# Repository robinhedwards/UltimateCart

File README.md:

Ultimate Cart
=============
The Ultimate Cart is an SD-card based multicart for the Atari 8-bit, which I've been developing for the last few months.
It allows you to browse the SD card on the atari and launch cartridge images from ROM and CAR files from the menu.
The PCB is designed to fit in a standard grey cartridge case (after a bit of modification with some clippers and a file).

It supports most ROMs up to 1 megabyte in size, including standard 8k and 16k cartridges, XEGS, AtariMax 1 & 8mbit ROMs,
SIC! Cart, Bounty Bob, OSS, SDX & Williams. ROM dumps can be easily converted into CAR format with my html/javascript
conversion utility, [RomToCar](http://htmlpreview.github.com/?https://github.com/robinhedwards/UltimateCart/master/RomToCar.html).

Update (Feb-2016)
-----------------
New firmware also allows XEX files (Atari executables) to be launched direct from the SD card.

PCB Images
----------

Bill of Materials
-----------------

The FPGA originally used was an engineering sample (ES) variant of the chip. The production version of the FPGA is now available
and can be used instead. The programming files for the ES seem to work fine on the production chip.

```
1 x PCB (eagle .brd file can be uploaded to e.g. OSH park)
1 x Altera 10M08SAE144C8G or ES variant (Mouser part #989-10M08SAE144C8G/ES)
1 x Alliance Memory AS6C8008-55ZIN (Mouser part #913-AS6C8008-55ZIN)
4 x IDT QS3245QG (Mouser part #972-QS3245QG)
1 x 1N4148 Diode SOD-123 (e.g. RS Stock # 700-3671)
1 x Abracon ASE-50.000MHZ-ET (Farnell order code #2467898)
1 x LD1117S33TR (Farnell order code #1202826)
1 x TE Connectivity 2041021-3 or -4 (Farnell order code #2112526, Mouser part #571-2041021-1)
1 x Shrouded box header 2x5 (e.g. Hobbytronics.co.uk - BOXHEAD25, Farnell order code #2215304)
1 x Momentary tactile switch Right Angled PCB Mount (ebay)
3 x 10uF 0805 Capacitors (e.g. Farnell order code #2320856)
11 x 0.1uF 0805 Capacitors (e.g. Farnell order code #1759143)
1 x 0.01uF 0805 Capacitor (e.g. Farnell order code #1759246)
9 x 10k 0805 Resistor (e.g. Farnell order code #2447553)
1 x 0805 LED (e.g. Farnell order code #1581239)
1 x 200ohm 0805 Resistor (e.g. Farnell order code #2447602)
1 x Header male 2x1 0.1" pitch
1 x 47k 0805 Resistor (e.g. Farnell order code #2447664) [v3 Board only]
```

Assembly
--------

Although the schematic, board file and assembled images above are probably sufficient by themselves
for a determined person to complete the board, here is the method I'm using to assemble the boards.

You will need:
```
Solder paste (I used standard chipquik unleaded) syringe
Some way of reflowing the board (e.g. cheap toaster oven)
Solder paste stencil for the fpga side (optional, but recommended - see below)
Tweezers (or a better tool) for placing the components
Soldering iron
Flux and braid to fix any bridged pins (you may not need if you use a stencil)
USB Blaster to program the fpga
Blu-tac I find useful for keeping things steady
```

You can either apply solder paste by hand (using a syringe) or using a stencil. Having done it both ways,
I'd say the ten pounds I spent on a stencil was the best money I've ever spent! You can get a stencil made
cheaply from a variety of places. I'd recommend either oshstencils (USA) or smtstencil.co.uk (UK). The
paste layer was not correct on the original board, but was corrected in the revised version.

Apply the solder paste to the fpga side of the board, making sure you don't forget the ground pad. The
revised board removes R11 (a pullup resistor on the SD card line) which is not required (since SD cards
have an internal pull-up on CS).

Then populate the components, with reference to the marks on the board and the images above.
Bake the board in an over until the paste melts (you'll see it shine), leave it for about 30s-1min, then open
the oven door and let it cool.

Apply solder paste to the other side of the board (leaving the SD card which is hand soldered). There is
less need for a stencil for this side of the board, a syringe is fine. Populate (make sure you get the polarity
of the LED and diode correct) and bake again.

Before you do any hand soldering, check for bridged pins on the ICs. Some pins are bridged on the PCB - thats ok.
Any others, use braid, flux and soldering iron to remove.

Next you will need to hand solder the jtag box header (slot facing outwards), and 2x1 male header.

Now is a good time to check for shorts - (1) between the +5V and GND pins of the male header, (2) between +3.3v
and GND on the regulator, and (3) between VCC and GND on the IDT quickswitches. If you find a short then STOP
and fix it. There will be a bridge somewhere. Refer to the eagle files to help identify the location.

Once that's done, you should be able to power up the board, plug in a USB blaster and program the chip from
Quartus (use the pof file - this permanently programs the chip). If successful you should see the LED on the
board blinking.

Finally, hand solder the SD card slot and reset button to the board. You're done!

Erratum (20-Oct-15)
-------
Someone who has built this project got in touch to report that some SD cards fail to be recognised.
It appears that a 10k-100k pullup is required on the SD card DO (pin 7), or some cards will fail to initialise.
I haven't come across this in the 10 different SD cards I've tested, but if you do have problems then you can fix
it by adding a 47k pull-up resistor as shown in the photo below.

Note (1-Mar-16) - I have now uploaded a revised version of the board (v3) which adds this resistor to the PCB (labelled R11).

3d Printed Cartridge Shell (13-Jul-17)
-------
I have added STL files (and the source files) so you can use a 3d printer to make a nice cartridge shell for your PCB.

Credits
-------
* Design, PCB & FPGA firmware by Robin Edwards (electrotrains at atariage)
* Atari boot menu & XEX loader by Jonathan Halliday (flashjazzcat at atariage)
* Debugging - Matthias Reichl (HiassofT at atariage)
* Help, suggestions and FAT32 LFN code from Mark Watson (foft at atariage)

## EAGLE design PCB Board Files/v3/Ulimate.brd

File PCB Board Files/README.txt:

Eagle files for the PCB.

v2 removes an un-needed pull-up resistor on the SD card CS line.
It also includes fixes to the paste layer so you can order a stencil from the board file.
Finally, it adds a funky logo to the top of the board to match the label.

v3 adds a 47k pull-up resistor (marked R11) to SD card as discussed in the erratum on the main page. R11 is on the SD card side of the board, near the SD card slot itself.

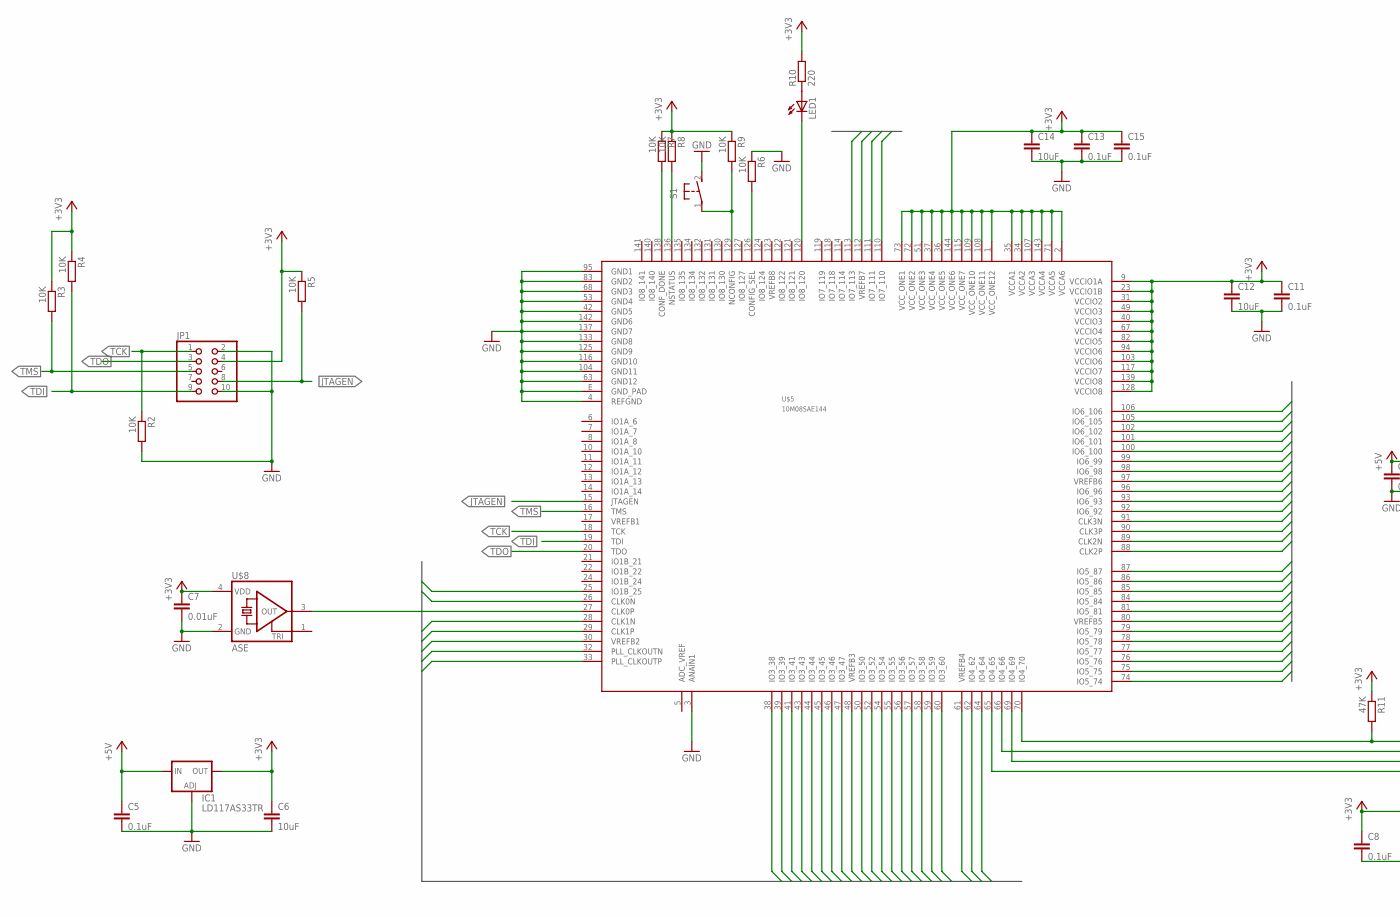
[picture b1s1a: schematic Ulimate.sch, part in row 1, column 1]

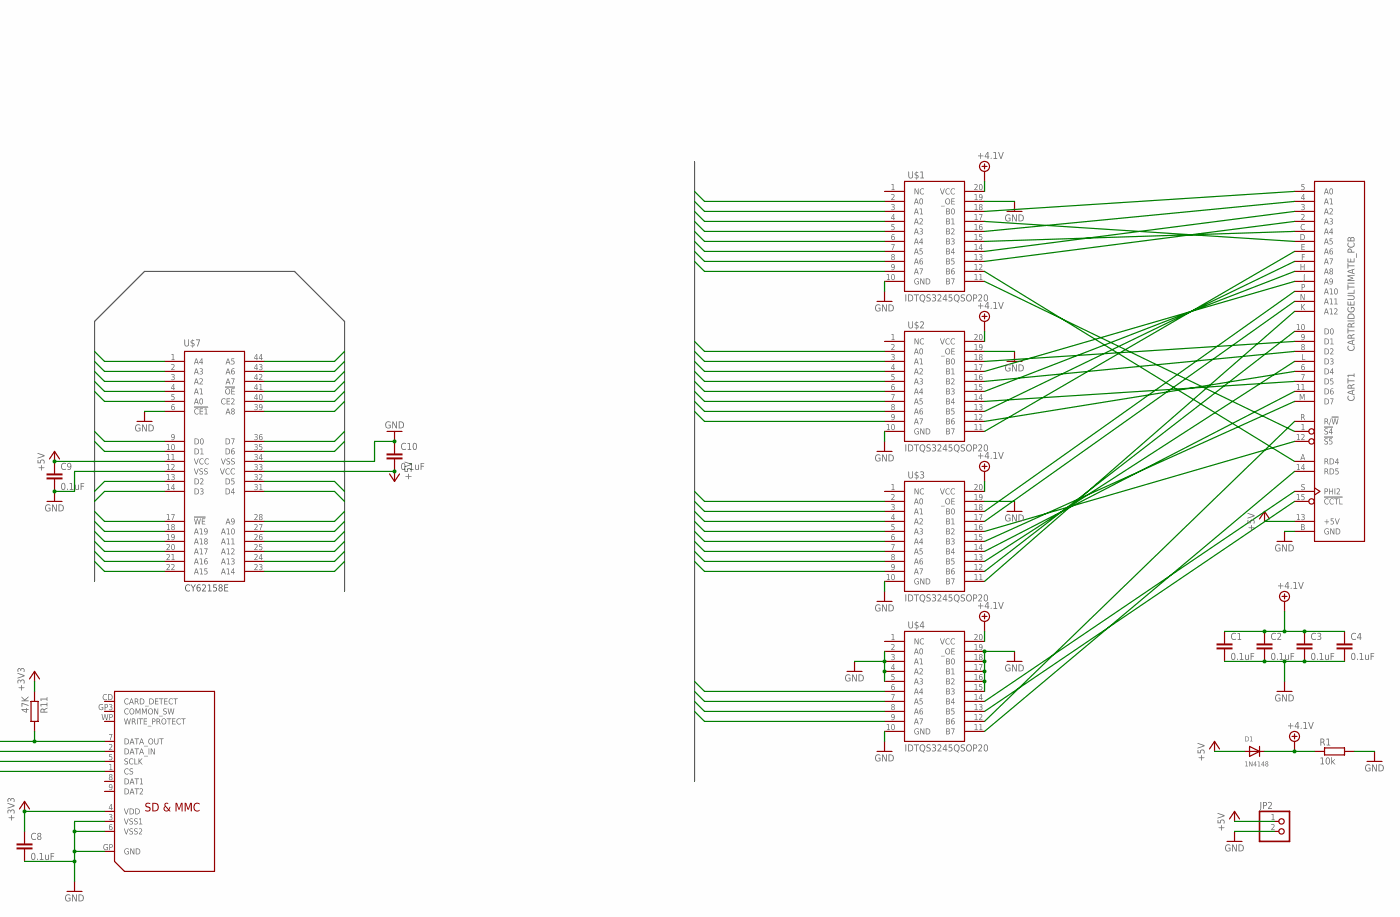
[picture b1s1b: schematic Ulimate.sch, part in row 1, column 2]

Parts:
C1, C2, C3, C4, C5, C8, C9, C10, C11, C13, C15: 0.1uF; C0805K
C6, C12, C14: 10uF; C0805K
C7: 0.01uF; C0805K
CART1: CARTRIDGEULTIMATE_PCB; CART_ULTIMATE
D1: 1N4148; SOD-123FL
IC1: LD117AS33TR; SOT223
JP1: PINHD-2X5; 2X05
JP2: PINHD-1X2; 1X02
LED1: LEDSML0805; SML0805
R1: 10k; R0805
R2, R3, R4, R5, R6, R7, R8, R9: 10K; R0805
R10: 220; R0805
R11: 47K; R0805
S1: 31-XXSKINNY; B3F-31XX-SKINNIER
U$1, U$2, U$3, U$4: IDTQS3245QSOP20; QSOP20
U$5: 10M08SAE144; EQFP144
U$6: SDMMC06132; 06132
U$7: CY62158E; TSOP44-II
U$8: ASE

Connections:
!OE: U$5.106 (IO6_106), U$7.41 (!OE)
!WE: U$5.89 (CLK2N), U$7.17 (!WE)
+3V3: C6.1, C7.1, C8.1, C11.1, C12.1, C13.1, C14.1, C15.1, IC1.4 (OUT), JP1.4, R3.1, R4.1, R5.1, R7.1, R8.1, R9.1, R10.2, R11.1, U$5.1 (VCC_ONE12), U$5.2 (VCCA6), U$5.9 (VCCIO1A), U$5.23 (VCCIO1B), U$5.31 (VCCIO2), U$5.34 (VCCA2), U$5.35 (VCCA1), U$5.36 (VCC_ONE5), U$5.37 (VCC_ONE4), U$5.40 (VCCIO3), U$5.49 (VCCIO3), U$5.51 (VCC_ONE3), U$5.67 (VCCIO4), U$5.71 (VCCA5), U$5.72 (VCC_ONE2), U$5.73 (VCC_ONE1), U$5.82 (VCCIO5), U$5.94 (VCCIO6), U$5.103 (VCCIO6), U$5.107 (VCCA3), U$5.108 (VCC_ONE11), U$5.109 (VCC_ONE10), U$5.115 (VCC_ONE7), U$5.117 (VCCIO7), U$5.128 (VCCIO8), U$5.139 (VCCIO8), U$5.143 (VCCA4), U$5.144 (VCC_ONE6), U$6.4 (VDD), U$8.4 (VDD)
+4.1V: C1.1, C2.1, C3.1, C4.1, D1.C, R1.1, U$1.20 (VCC), U$2.20 (VCC), U$3.20 (VCC), U$4.20 (VCC)
+5V: C5.1, C9.1, C10.2, CART1.13 (+5V), D1.A, IC1.3 (IN), JP2.1, U$7.11 (VCC), U$7.33 (VCC)
A0: U$5.96 (IO6_96), U$7.5 (A0)
A1: U$5.97 (VREFB6), U$7.4 (A1)
A2: U$5.98 (IO6_98), U$7.3 (A2)
A3: U$5.99 (IO6_99), U$7.2 (A3)
A4: U$5.100 (IO6_100), U$7.1 (A4)
A5: U$5.105 (IO6_105), U$7.44 (A5)
A6: U$5.102 (IO6_102), U$7.43 (A6)
A7: U$5.101 (IO6_101), U$7.42 (A7)
A8: U$5.111 (IO7_111), U$7.39 (A8)
A9: U$5.76 (IO5_76), U$7.28 (A9)
A10: U$5.77 (IO5_77), U$7.27 (A10)
A11: U$5.78 (IO5_78), U$7.26 (A11)
A12: U$5.79 (IO5_79), U$7.25 (A12)
A13: U$5.80 (VREFB5), U$7.24 (A13)
A14: U$5.81 (IO5_81), U$7.23 (A14)
A15: U$5.84 (IO5_84), U$7.22 (A15)
A16: U$5.85 (IO5_85), U$7.21 (A16)
A17: U$5.86 (IO5_86), U$7.20 (A17)
A18: U$5.87 (IO5_87), U$7.19 (A18)
A19: U$5.88 (CLK2P), U$7.18 (A19)
CART_A0: U$1.2 (A0), U$5.39 (IO3_39)
CART_A1: U$1.4 (A2), U$5.33 (PLL_CLKOUTP)
CART_A2: U$1.6 (A4), U$5.30 (VREFB2)
CART_A3: U$1.7 (A5), U$5.29 (CLK1P)
CART_A4: U$1.5 (A3), U$5.32 (PLL_CLKOUTN)
CART_A5: U$1.3 (A1), U$5.38 (IO3_38)
CART_A6: U$2.9 (A7), U$5.41 (IO3_41)
CART_A7: U$2.7 (A5), U$5.44 (IO3_44)
CART_A8: U$2.5 (A3), U$5.46 (IO3_46)
CART_A9: U$2.3 (A1), U$5.48 (VREFB3)
CART_A10: U$3.2 (A0), U$5.60 (IO3_60)
CART_A11: U$3.3 (A1), U$5.59 (IO3_59)
CART_A12: U$3.9 (A7), U$5.52 (IO3_52)
CART_CTL: U$4.7 (A5), U$5.64 (IO4_64)
CART_D0: U$3.8 (A6), U$5.54 (IO3_54)
CART_D1: U$2.2 (A0), U$5.50 (IO3_50)
CART_D2: U$2.4 (A2), U$5.47 (IO3_47)
CART_D3: U$3.7 (A5), U$5.55 (IO3_55)
CART_D4: U$2.8 (A6), U$5.43 (IO3_43)
CART_D5: U$2.6 (A4), U$5.45 (IO3_45)
CART_D6: U$3.6 (A4), U$5.56 (IO3_56)
CART_D7: U$3.5 (A3), U$5.57 (IO3_57)
CART_PHI: U$4.6 (A4), U$5.26 (CLK0N)
CART_RD4: U$1.8 (A6), U$5.25 (IO1B_25)
CART_RD5: U$4.9 (A7), U$5.61 (VREFB4)
CART_RW: U$4.8 (A6), U$5.62 (IO4_62)
CART_S4: U$1.9 (A7), U$5.28 (CLK1N)
CART_S5: U$3.4 (A2), U$5.58 (IO3_58)
CE: U$5.110 (IO7_110), U$7.40 (CE2)
D0: U$5.93 (IO6_93), U$7.9 (D0)
D1: U$5.92 (IO6_92), U$7.10 (D1)
D2: U$5.91 (CLK3N), U$7.13 (D2)
D3: U$5.90 (CLK3P), U$7.14 (D3)
D4: U$5.75 (IO5_75), U$7.31 (D4)
D5: U$5.74 (IO5_74), U$7.32 (D5)
D6: U$5.113 (IO7_113), U$7.35 (D6)
D7: U$5.112 (VREFB7), U$7.36 (D7)
GND: C1.2, C2.2, C3.2, C4.2, C5.2, C6.2, C7.2, C8.2, C9.2, C10.1, C11.2, C12.2, C13.2, C14.2, C15.2, CART1.B (GND), IC1.1 (ADJ), JP1.2, JP1.10, JP2.2, R1.2, R2.2, R6.1, S1.2 (S), U$1.10 (GND), U$1.19 (_OE), U$2.10 (GND), U$2.19 (_OE), U$3.10 (GND), U$3.19 (_OE), U$4.2 (A0), U$4.3 (A1), U$4.4 (A2), U$4.5 (A3), U$4.10 (GND), U$4.15 (B3), U$4.16 (B2), U$4.17 (B1), U$4.18 (B0), U$4.19 (_OE), U$5.3 (ANAIN1), U$5.4 (REFGND), U$5.42 (GND5), U$5.53 (GND4), U$5.63 (GND12), U$5.68 (GND3), U$5.83 (GND2), U$5.95 (GND1), U$5.104 (GND11), U$5.116 (GND10), U$5.125 (GND9), U$5.133 (GND8), U$5.137 (GND7), U$5.142 (GND6), U$5.E (GND_PAD), U$6.3 (VSS1), U$6.6 (VSS2), U$6.GP (GND), U$7.6 (!CE1), U$7.12 (VSS), U$7.34 (VSS), U$8.2 (GND)
JTAGEN: JP1.8, R5.2, U$5.15 (JTAGEN)
unnamed: CART1.1 (!S4), U$1.11 (B7)
unnamed: CART1.A (RD4), U$1.12 (B6)
unnamed: CART1.2 (A3), U$1.13 (B5)
unnamed: CART1.3 (A2), U$1.14 (B4)
unnamed: CART1.C (A4), U$1.15 (B3)
unnamed: CART1.4 (A1), U$1.16 (B2)
unnamed: CART1.D (A5), U$1.17 (B1)
unnamed: CART1.5 (A0), U$1.18 (B0)
unnamed: CART1.E (A6), U$2.11 (B7)
unnamed: CART1.6 (D4), U$2.12 (B6)
unnamed: CART1.F (A7), U$2.13 (B5)
unnamed: CART1.7 (D5), U$2.14 (B4)
unnamed: CART1.H (A8), U$2.15 (B3)
unnamed: CART1.8 (D2), U$2.16 (B2)
unnamed: CART1.J (A9), U$2.17 (B1)
unnamed: CART1.9 (D1), U$2.18 (B0)
unnamed: CART1.K (A12), U$3.11 (B7)
unnamed: CART1.10 (D0), U$3.12 (B6)
unnamed: CART1.L (D3), U$3.13 (B5)
unnamed: CART1.11 (D6), U$3.14 (B4)
unnamed: CART1.M (D7), U$3.15 (B3)
unnamed: CART1.12 (!S5), U$3.16 (B2)
unnamed: CART1.N (A11), U$3.17 (B1)
unnamed: CART1.P (A10), U$3.18 (B0)
unnamed: CART1.14 (RD5), U$4.11 (B7)
unnamed: CART1.R (R/!W), U$4.12 (B6)
unnamed: CART1.15 (!CCTL), U$4.13 (B5)
unnamed: CART1.S (PHI2), U$4.14 (B4)
unnamed: U$5.27 (CLK0P), U$8.3 (OUT)
unnamed: R6.2, U$5.126 (CONFIG_SEL)
unnamed: R7.2, U$5.138 (CONF_DONE)
unnamed: R8.2, U$5.136 (NSTATUS)
unnamed: R9.2, S1.1, U$5.129 (NCONFIG)
unnamed: LED1.A, R10.1
unnamed: LED1.C, U$5.120 (IO8_120)
SD_CLK: U$5.69 (IO4_69), U$6.5 (SCLK)
SD_CS: U$5.65 (IO4_65), U$6.1 (CS)
SD_DI: U$5.66 (IO4_66), U$6.2 (DATA_IN)
SD_DO: R11.2, U$5.70 (IO4_70), U$6.7 (DATA_OUT)
TCK: JP1.1, R2.1, U$5.18 (TCK)
TDI: JP1.9, R4.2, U$5.19 (TDI)
TDO: JP1.3, U$5.20 (TDO)
TMS: JP1.5, R3.2, U$5.16 (TMS)

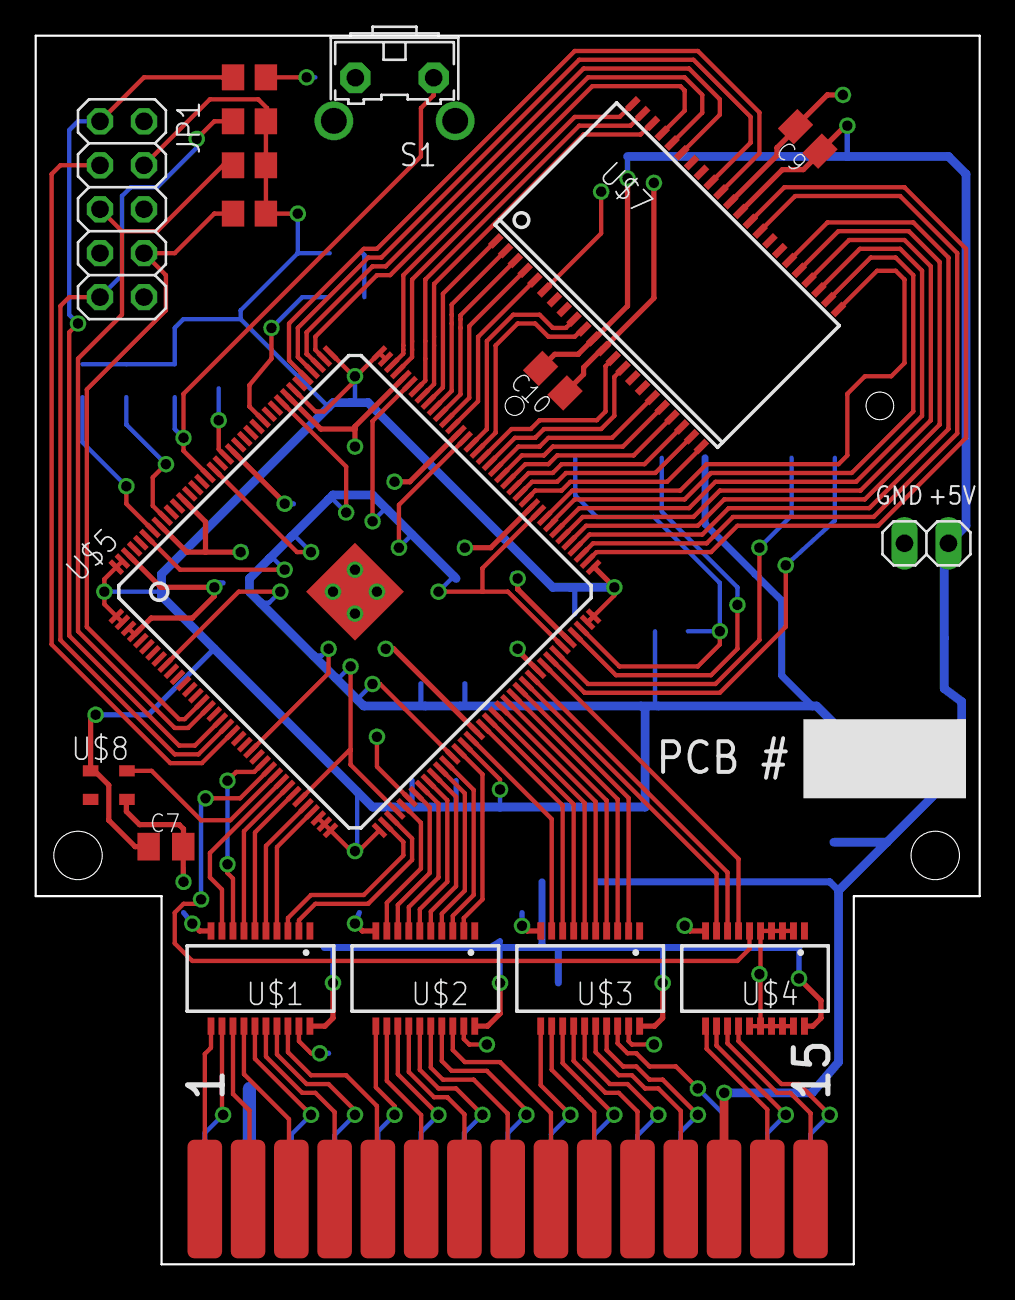
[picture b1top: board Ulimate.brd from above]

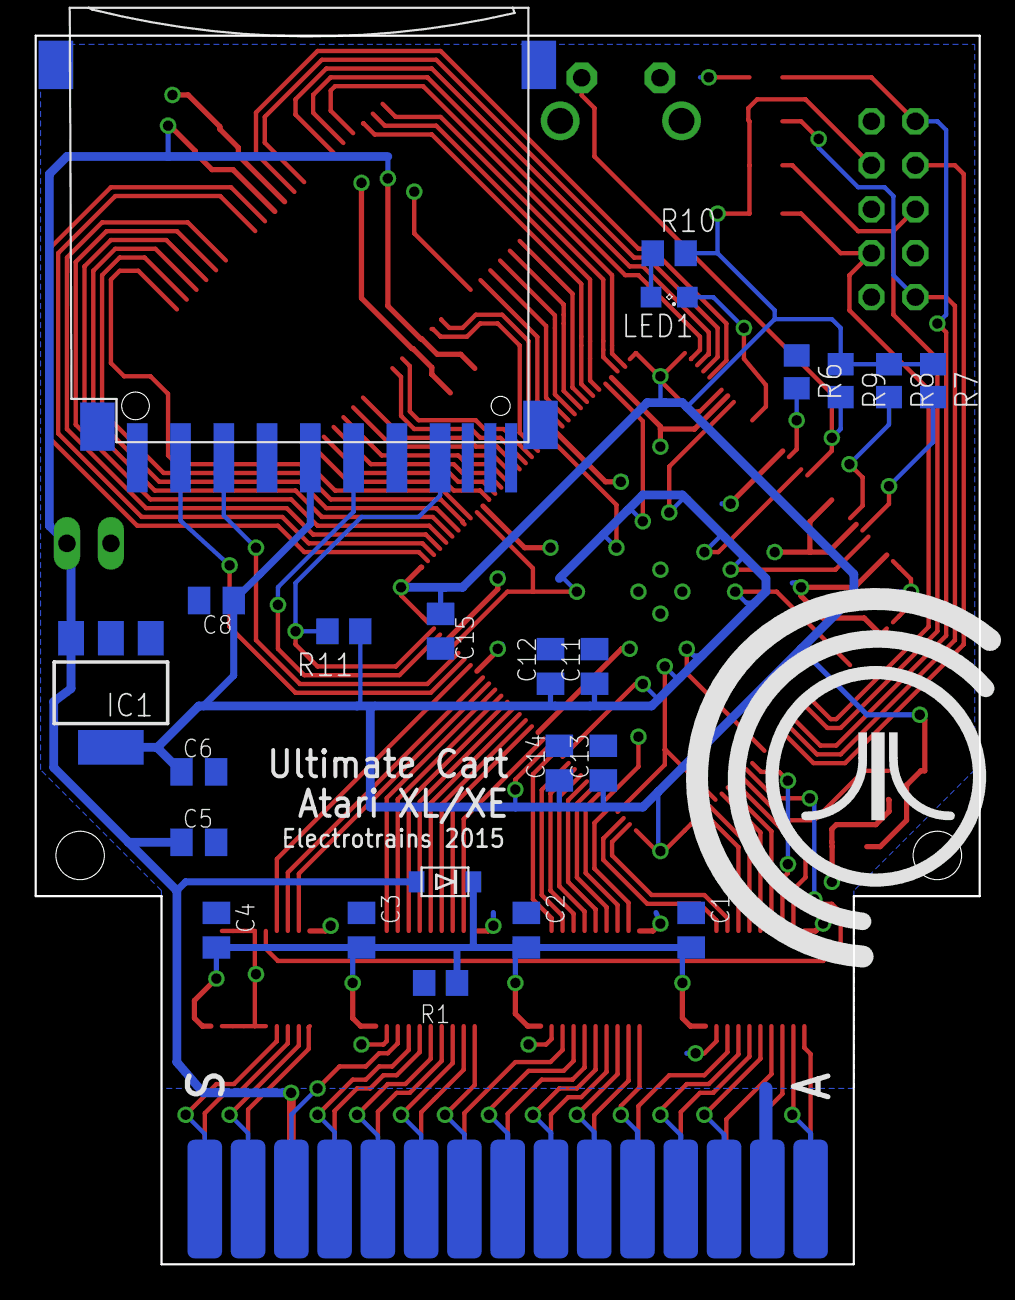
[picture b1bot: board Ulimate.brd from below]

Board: 2 copper layers, 54.5 x 71.0 mm, 41 parts (23 on the bottom side), 107 nets.

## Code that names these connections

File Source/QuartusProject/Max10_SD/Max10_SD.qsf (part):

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set_global_assignment -name PARTITION_COLOR 16764057 -section_id Top
set_location_assignment PIN_27 -to CLK
set_location_assignment PIN_120 -to LED[0]
set_location_assignment PIN_61 -to CART_RD5
set_location_assignment PIN_58 -to CART_S5
set_location_assignment PIN_25 -to CART_RD4
set_location_assignment PIN_28 -to CART_S4
set_location_assignment PIN_39 -to CART_ADDR[0]
set_location_assignment PIN_33 -to CART_ADDR[1]
set_location_assignment PIN_30 -to CART_ADDR[2]
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set_instance_assignment -name IO_STANDARD "3.3 V SCHMITT TRIGGER" -to CART_PHI2
set_instance_assignment -name IO_STANDARD "3.3-V LVTTL" -to CART_CTL
set_instance_assignment -name IO_STANDARD "3.3-V LVTTL" -to CART_RW
set_location_assignment PIN_64 -to CART_CTL
set_location_assignment PIN_26 -to CART_PHI2
set_location_assignment PIN_62 -to CART_RW
set_global_assignment -name CDF_FILE Max10_SD.cdf
set_instance_assignment -name IO_STANDARD "3.3-V LVTTL" -to LED[1]
set_instance_assignment -name IO_STANDARD "3.3-V LVTTL" -to LED[2]
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
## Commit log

2015-08-17 initial commit of board files
2015-08-17 add BOM
2015-08-17 fix BOM
2015-08-20 Add programming files
2015-08-21 add images, CAR utility
2015-08-21 remove repeat image
2015-08-21 fix link
2015-08-21 add new section
2015-08-24 add boot rom src, labels
2015-08-28 add doc
2015-09-10 Add Quartus II project
2015-09-10 remove default README.txt file
2015-09-14 updates to documentation
2015-09-22 update pcb
2015-09-27 add assembly instructions
2015-09-27 fix typos
2015-09-27 more typos
2015-09-27 forgot to mention oven
2015-10-08 updates to BOM
2015-10-20 add erratum re SD card pullup
2015-10-27 change data-bus sampling
2015-10-30 fixes signal integrity issues on XL machines
2016-02-15 add new firmware with XEX loading
2016-02-15 documentation update
2016-02-16 fix bug with start/end of list
2016-03-01 add v3 board with 47k resistor
2016-03-02 update docs
2016-04-04 XEX loader source, update project to Quartus 15.1
2017-07-13 add STL files for shell
2019-06-29 Update atari_rom.vhd
    FPGA always drives data bus drivers when /S4 or /S5 is pulled low.
    It should mask the read data according to the state of RD4 & RD5:
2021-06-09 Update avr-objcopy.exe
    version is updated, it does not need external DLLs to run. GNU objcopy (GNU Binutils) 2.36.1
2021-06-10 Update atari_rom.vhd
    Fix for Atari 800 S4 & S5 are always active. Only the RAM is not mapped when RD4, RD5 is driven high
2021-06-11 TURBOSOFT cartridge
    Support for TURBOSOFT 64k and 128k cartridges.
2021-06-15 ATRAX cartridge
    Support for Atrax 128K cartridges.
2021-06-25 Patch for DLI
    DLI flicker fixed
    Contribution from flashjazzcat
2021-06-25 Patch for .XEX
    BOOT? set to 1
    CRITIC asserted during segment reads
    RAM clearing (including stack) beefed up
    Contribution from flashjazzcat
2021-08-03 Update Boot.asm
    back to original charger
2021-08-28 4k cartridge support
    added support for 4k cartridges, simulating an 8k cartridge that its first 4k is FF and the rest is the game to be loaded.
2021-08-29 New firmware
    new firmware 2021-08-28
2023-04-26 New firmware (#5)
    * Update avr-objcopy.exe
    version is updated, it does not need external DLLs to run. GNU objcopy (GNU Binutils) 2.36.1
    * Update atari_rom.vhd
    Fix for Atari 800 S4 & S5 are always active. Only the RAM is not mapped when RD4, RD5 is driven high
    * TURBOSOFT cartridge
    Support for TURBOSOFT 64k and 128k cartridges.
2023-09-30 more car types
    Adds all the cart types supported by Ultimate cart, UnoCart and A8PicoCart
2023-09-30 update wording

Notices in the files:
Source/QuartusProject/Max10_SD/Max10_SD.qsf:
Copyright (C) 1991-2014 Altera Corporation. All rights reserved.
parts and their libraries:
eagle-6.5.0-atari: Copyright (c) 2010
Copyright (c) 2009
This library is licensed under the
Creative Commons Attribution 3.0 United States License.
